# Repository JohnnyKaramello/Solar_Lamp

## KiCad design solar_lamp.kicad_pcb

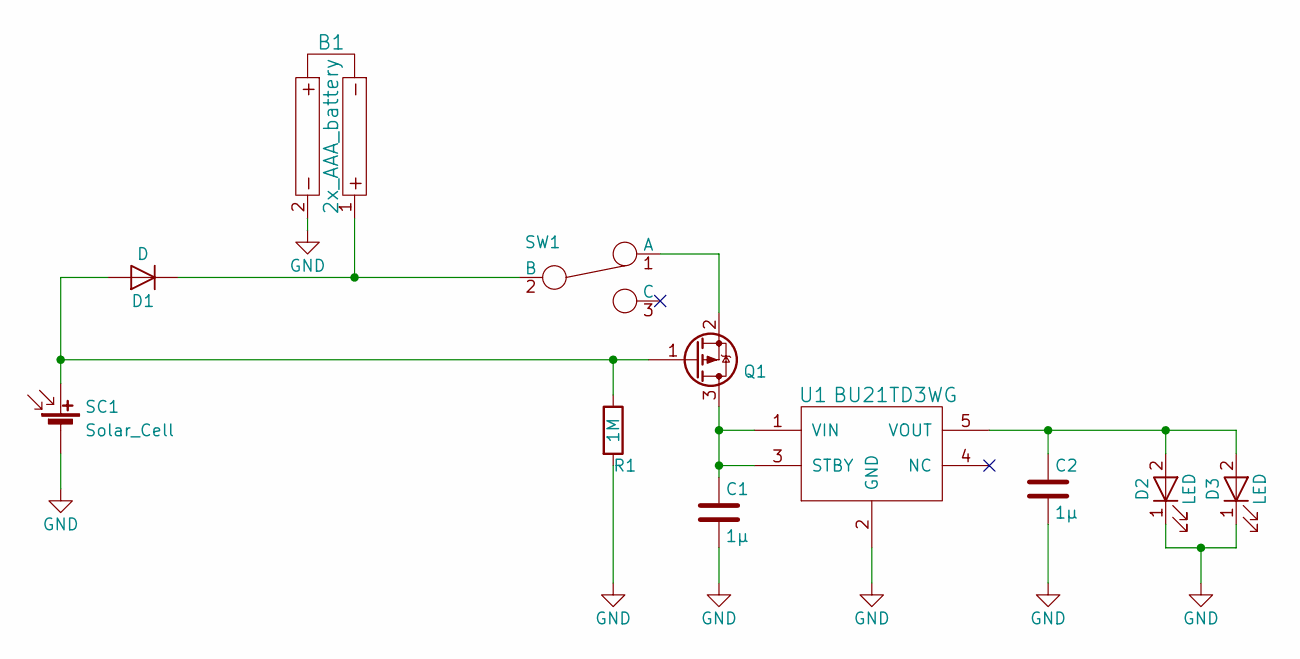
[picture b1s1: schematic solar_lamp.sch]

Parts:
B1: 2x_AAA_battery; Battery_Holder_Keystone_2468
C1, C2: 1µ; C_0603
D1: D; SOD-523F; MFG Part Num RB751S40
D2, D3: LED; LED-5MM
Q1: BSS84PH6327XTSA2; SOT-23
R1: 1M; R_0603
SC1: Solar_Cell; Adafruit_round_solar_panel
SW1: Switch_SPDT; DPDT_SMT; MFG Part Num JS202011SCQN
U1: BU21TD3WG; SSOP5; MFG Part Num BU21TD3WG

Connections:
GND: B1.2, C1.2, C2.2, D2.1 (K), D3.1 (K), R1.2, SC1.2 (-), U1.2 (GND)
unnamed: B1.1, D1.1 (K), SW1.2 (B)
unnamed: C1.1, Q1.3 (D), U1.1 (VIN), U1.3 (STBY)
unnamed: C2.1, D2.2 (A), D3.2 (A), U1.5 (VOUT)
unnamed: D1.2 (A), Q1.1 (G), R1.1, SC1.1 (+)
unnamed: Q1.2 (S), SW1.1 (A)

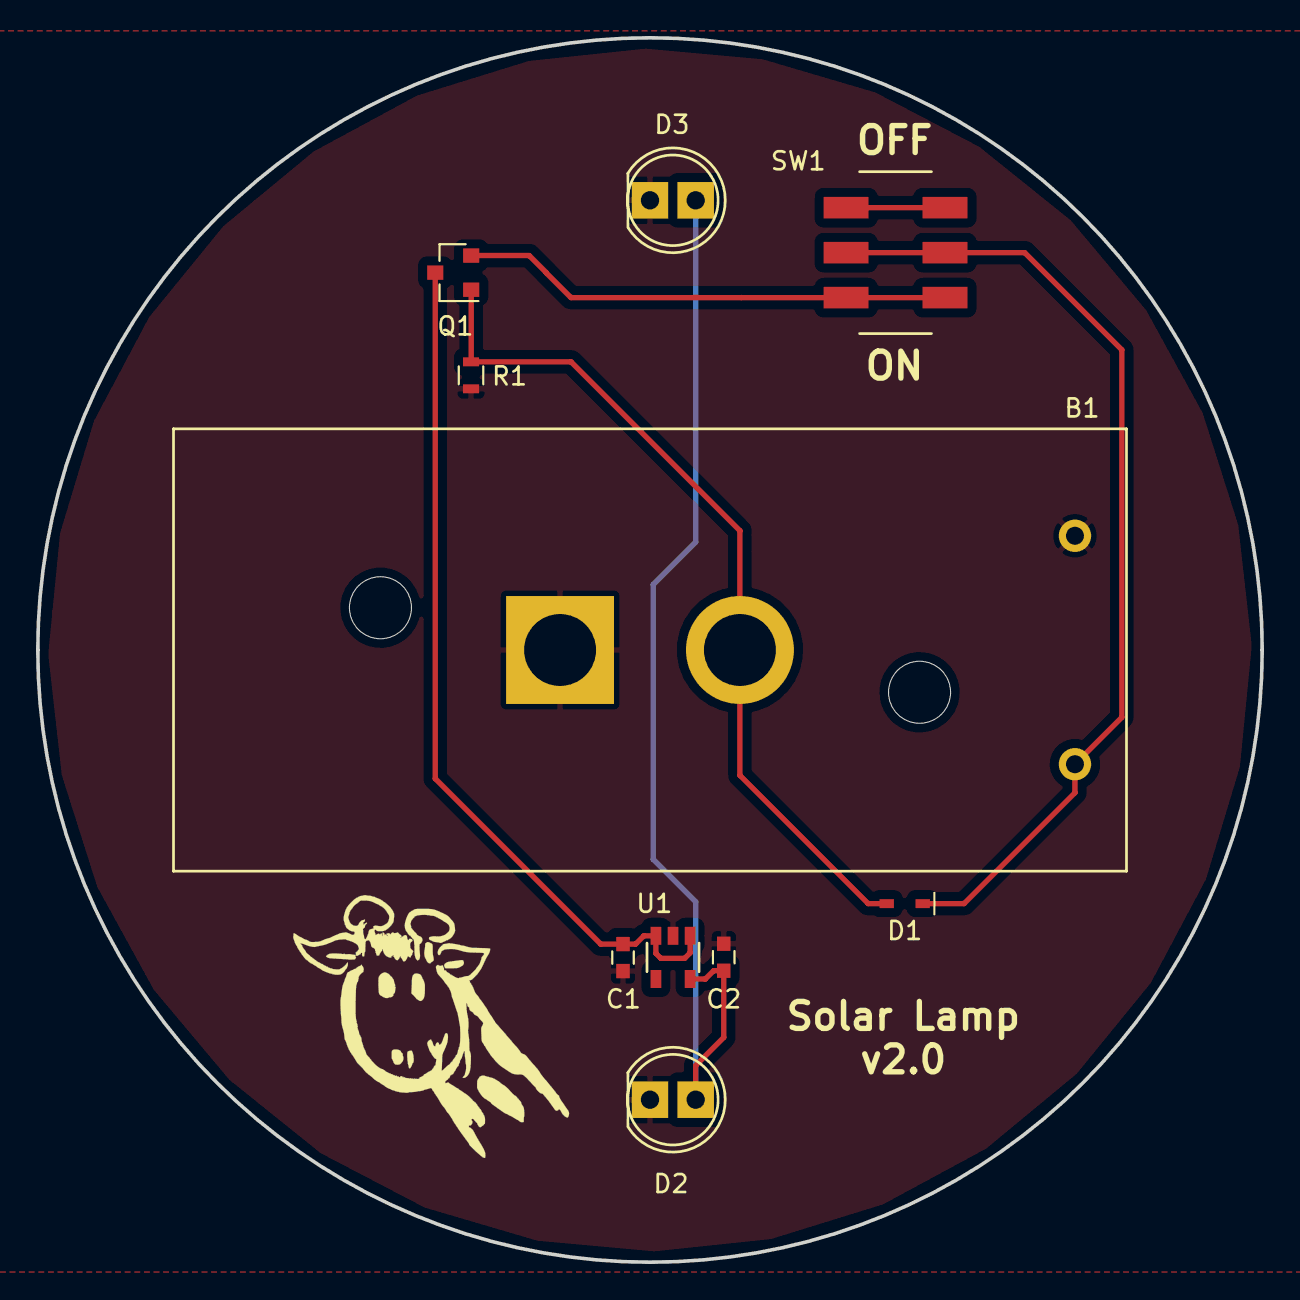
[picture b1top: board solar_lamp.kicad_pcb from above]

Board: 2 copper layers, 68.1 x 68.1 mm, 11 parts (1 on the bottom side), 6 nets.

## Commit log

2017-03-05 redraw schematic
2017-03-17 update schem/change components
2017-03-19 chose transistor/ update footprints
2017-03-20 preliminary layout
2017-03-21 changes in silkscreen
2017-03-21 repositioned diode
2017-03-22 add logo to silkscreen
